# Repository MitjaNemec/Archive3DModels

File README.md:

# KiCad Archive 3D models plugin

This plugin copies footprint 3D models to the project local subfolder (default name: packages3D). The plugin also updates the links to the models within the layout (.kicad_pcb) file so that they point to the archived 3D models with a path relative to the project folder.

If the footprint is updated, the 3Dmodel path is also updated. Thus the plugin should be re-run.

**Author :** doc.dr. Mitja Nemec

**Date :** 2025

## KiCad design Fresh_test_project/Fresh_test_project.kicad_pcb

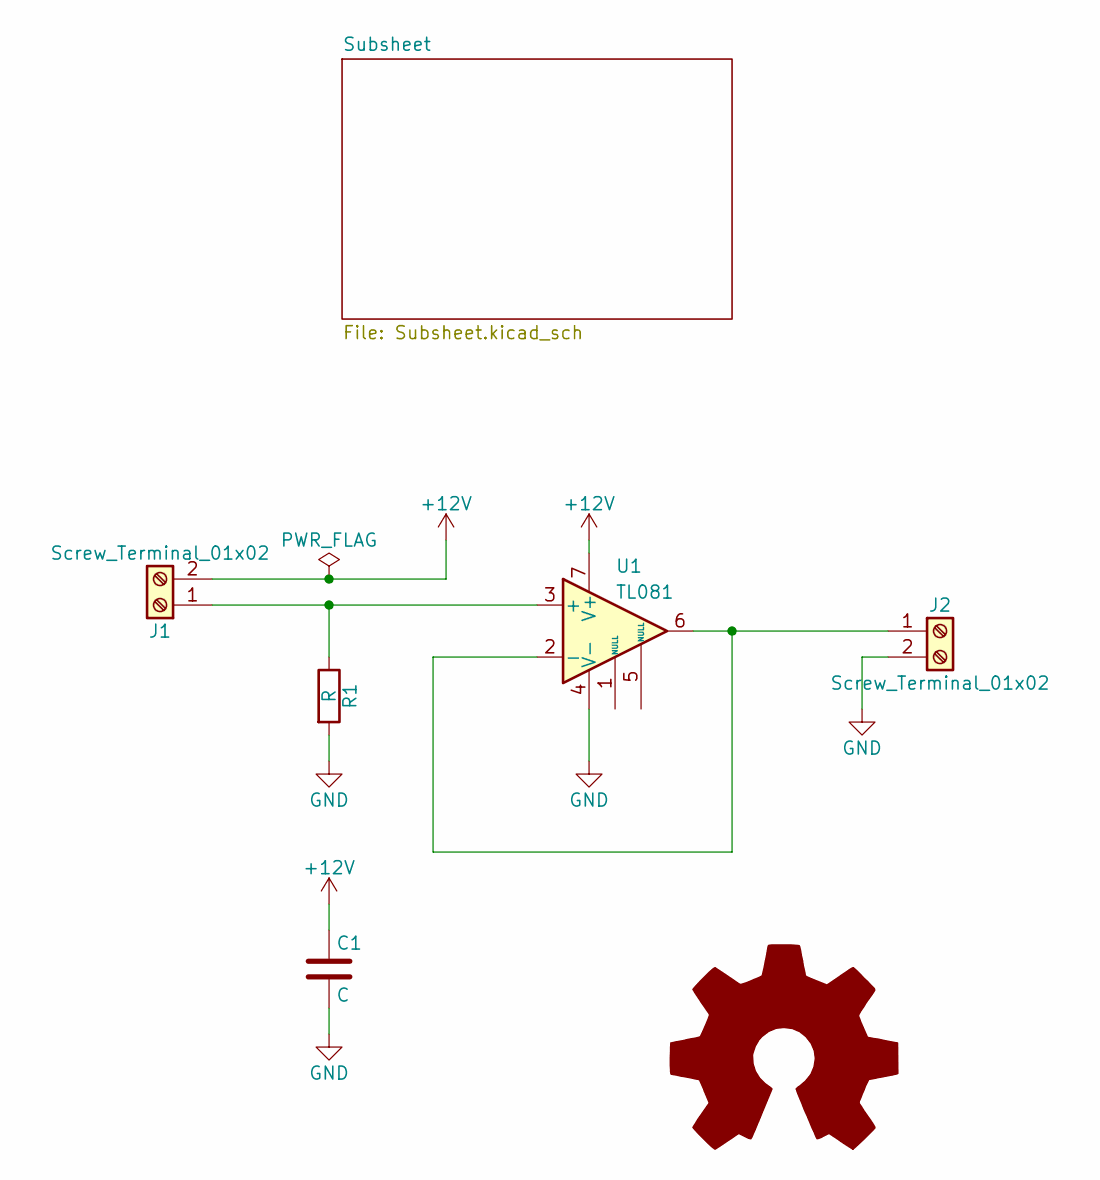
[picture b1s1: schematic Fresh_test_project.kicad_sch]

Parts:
C1: C; C_1206_3216Metric_Pad1.33x1.80mm_HandSolder
J1: Screw_Terminal_01x02; PhoenixContact_MSTBVA_2,5_2-G-5,08_1x02_P5.08mm_Vertical
J2: Screw_Terminal_01x02; PinHeader_1x02_P2.54mm_Vertical
R1: R; R_1206_3216Metric_Pad1.30x1.75mm_HandSolder
U1: TL081; DIP-8_W7.62mm

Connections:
+12V: C1.1, J1.2, U1.7 (V+)
GND: C1.2, J2.2, R1.2, U1.4 (V-); also elsewhere on the board
unnamed: J1.1, R1.1, U1.3 (+)
unnamed: J2.1, U1.2 (-), U1.6

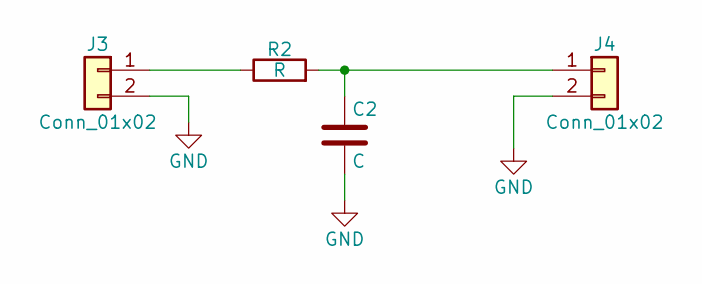
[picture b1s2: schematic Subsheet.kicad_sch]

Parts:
C2: C; C_0805_2012Metric
J3: Conn_01x02; PinHeader_1x02_P2.54mm_Vertical
J4: Conn_01x02; PinHeader_1x02_P2.00mm_Vertical
R2: R; R_1206_3216Metric_Pad1.30x1.75mm_HandSolder

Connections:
GND: C2.2, J3.2, J4.2; also elsewhere on the board
unnamed: C2.1, J4.1, R2.2
unnamed: J3.1, R2.1

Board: 2 copper layers, 9 parts (0 on the bottom side), 6 nets, no tracks yet.

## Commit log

2022-01-06 Initial commit of code
2022-01-07 - Added copy option to report dialog - clean up debug code - modify make_a_package.sh script
2022-01-07 Wrap the call to backend into try,except block to catch and log exceptions
2022-01-07 Add metadata_source.json
2022-01-07 remove metadata.json
2022-01-07 Delete metadata.json
    this file will be derived from metadata_source.json
2022-01-07 License change
2022-01-07 minor GUI design corrections, minor make_a_package.sh script corrections
2022-01-07 debugging the release process
2022-01-11 add proper window handling, minor cleanup
2022-01-14 Added test project
2022-01-14 remove any references to module(s)
2022-01-14 Added readme
2022-02-09 various fixes (package generatio, test project setup, testing code, ...)
2022-02-09 wx frame handler fix
2022-02-18 Style corrections
2022-10-27 Improve error dialog
2022-12-05 Another bugfix
2023-01-20 Remove wxhyperlinkctrl
2023-01-23 Revert removal of wxhyperlinkctrl
2023-02-20 V7 compatibility, minor improvements/text corrections
2023-05-05 Support $(...) syntax; substitute KISYS3DMOD and KICAD*_3DMODEL_DIR
2023-08-11 Handle uppercase extensions
    Fixes #5
2024-03-04 increase max kicad version to cover V8
2024-05-13 Update test project
2024-05-13 fix archiving multiple models
2025-01-07 Support command-line interface to archive 3D models.
2025-03-22 confirmed it works with V9, changed metadata version filter and bumped version for new release
2025-03-22 Add V9 3D path definitions
2025-04-01 Add deprecation warning
2026-04-08 Dodal avtorstvo
2026-04-08 Rename plugin in README to 'KiCad Archive 3D models'
    Updated the title of the README to reflect the plugin's name.
